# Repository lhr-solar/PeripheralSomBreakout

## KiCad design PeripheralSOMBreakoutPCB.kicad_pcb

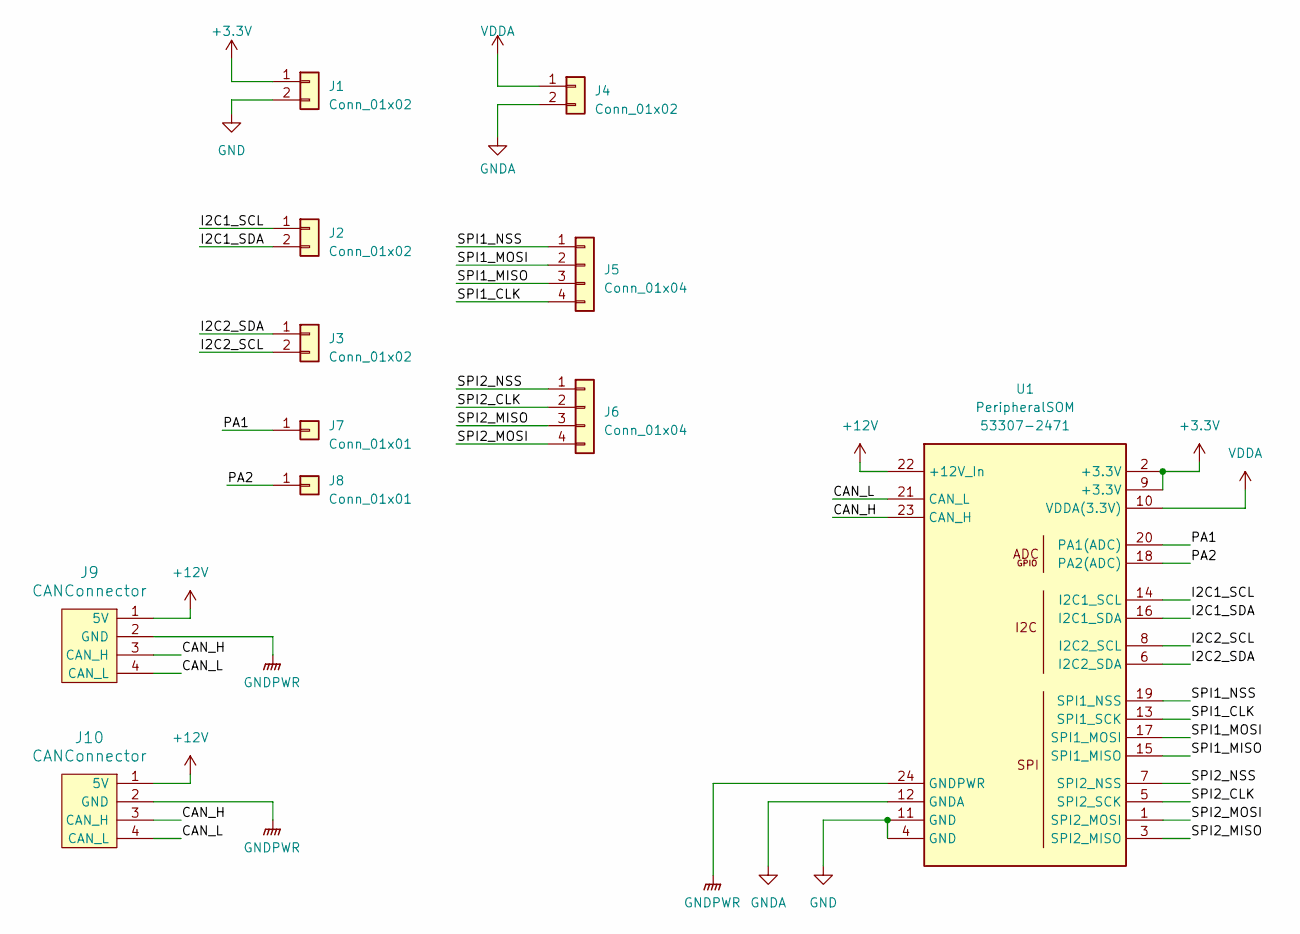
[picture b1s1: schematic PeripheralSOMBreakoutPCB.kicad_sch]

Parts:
J1, J2, J3, J4: Conn_01x02; PinHeader_1x02_P2.54mm_Vertical
J5, J6: Conn_01x04; PinHeader_1x04_P2.54mm_Vertical
J7, J8: Conn_01x01; PinHeader_1x01_P2.54mm_Vertical
J9, J10: CANConnector; Molex_MicroFit3.0_1x4xP3.00mm_PolarizingPeg_Vertical
U1: PeripheralSOM

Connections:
+3.3V: J1.1, U1.2 (+3.3V), U1.9 (+3.3V)
+12V: J9.1 (5V), J10.1 (5V), U1.22 (+12V_In)
/CAN_H: J9.3 (CAN_H), J10.3 (CAN_H), U1.23 (CAN_H)
/CAN_L: J9.4 (CAN_L), J10.4 (CAN_L), U1.21 (CAN_L)
/I2C1_SCL: J2.1, U1.14 (I2C1_SCL)
/I2C1_SDA: J2.2, U1.16 (I2C1_SDA)
/I2C2_SCL: J3.2, U1.8 (I2C2_SCL)
/I2C2_SDA: J3.1, U1.6 (I2C2_SDA)
/PA1: J7.1, U1.20 (PA1(ADC))
/PA2: J8.1, U1.18 (PA2(ADC))
/SPI1_CLK: J5.4, U1.13 (SPI1_SCK)
/SPI1_MISO: J5.3, U1.15 (SPI1_MISO)
/SPI1_MOSI: J5.2, U1.17 (SPI1_MOSI)
/SPI1_NSS: J5.1, U1.19 (SPI1_NSS)
/SPI2_CLK: J6.2, U1.5 (SPI2_SCK)
/SPI2_MISO: J6.3, U1.3 (SPI2_MISO)
/SPI2_MOSI: J6.4, U1.1 (SPI2_MOSI)
/SPI2_NSS: J6.1, U1.7 (SPI2_NSS)
GND: J1.2, U1.4 (GND), U1.11 (GND)
GNDA: J4.2, U1.12 (GNDA)
GNDPWR: J9.2 (GND), J10.2 (GND), U1.24 (GNDPWR)
VDDA: J4.1, U1.10 (VDDA(3.3V))

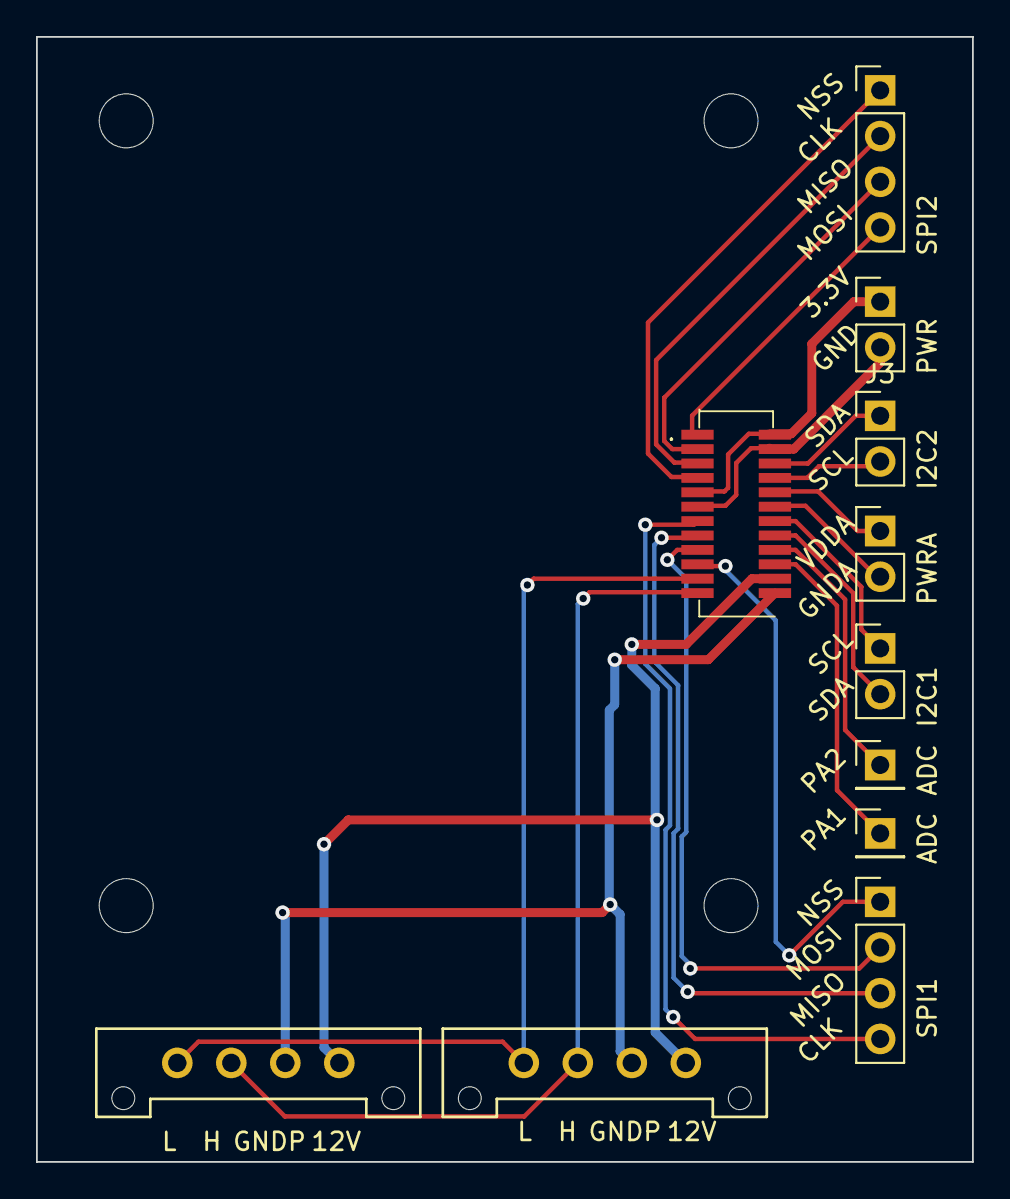
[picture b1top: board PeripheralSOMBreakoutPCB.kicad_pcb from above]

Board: 2 copper layers, 52.0 x 62.5 mm, 11 parts (0 on the bottom side), 22 nets.

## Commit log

2024-05-06 done
2024-05-06 gerbers done
2024-10-14 board
2024-10-14 add gerbers
